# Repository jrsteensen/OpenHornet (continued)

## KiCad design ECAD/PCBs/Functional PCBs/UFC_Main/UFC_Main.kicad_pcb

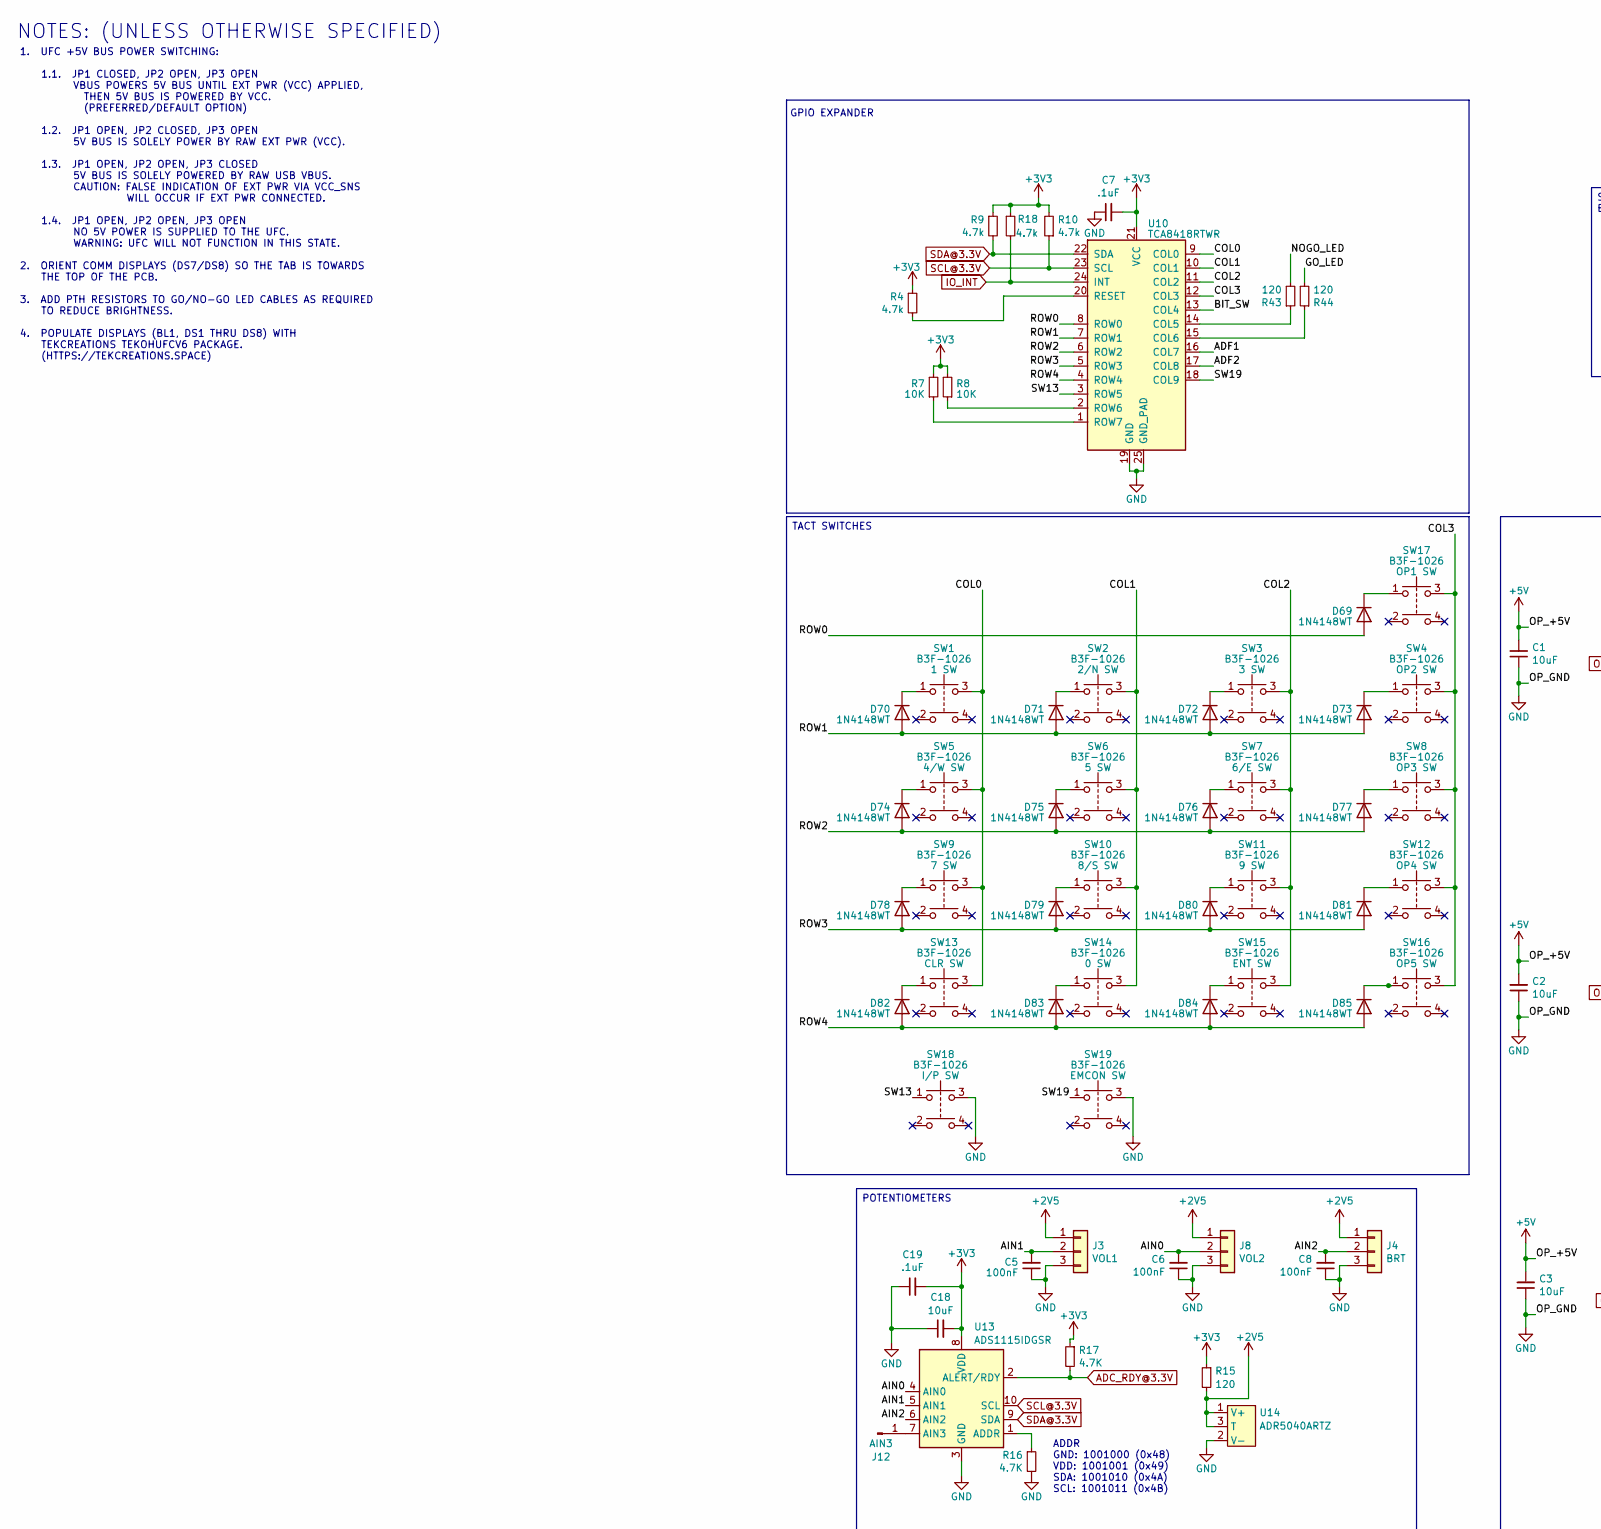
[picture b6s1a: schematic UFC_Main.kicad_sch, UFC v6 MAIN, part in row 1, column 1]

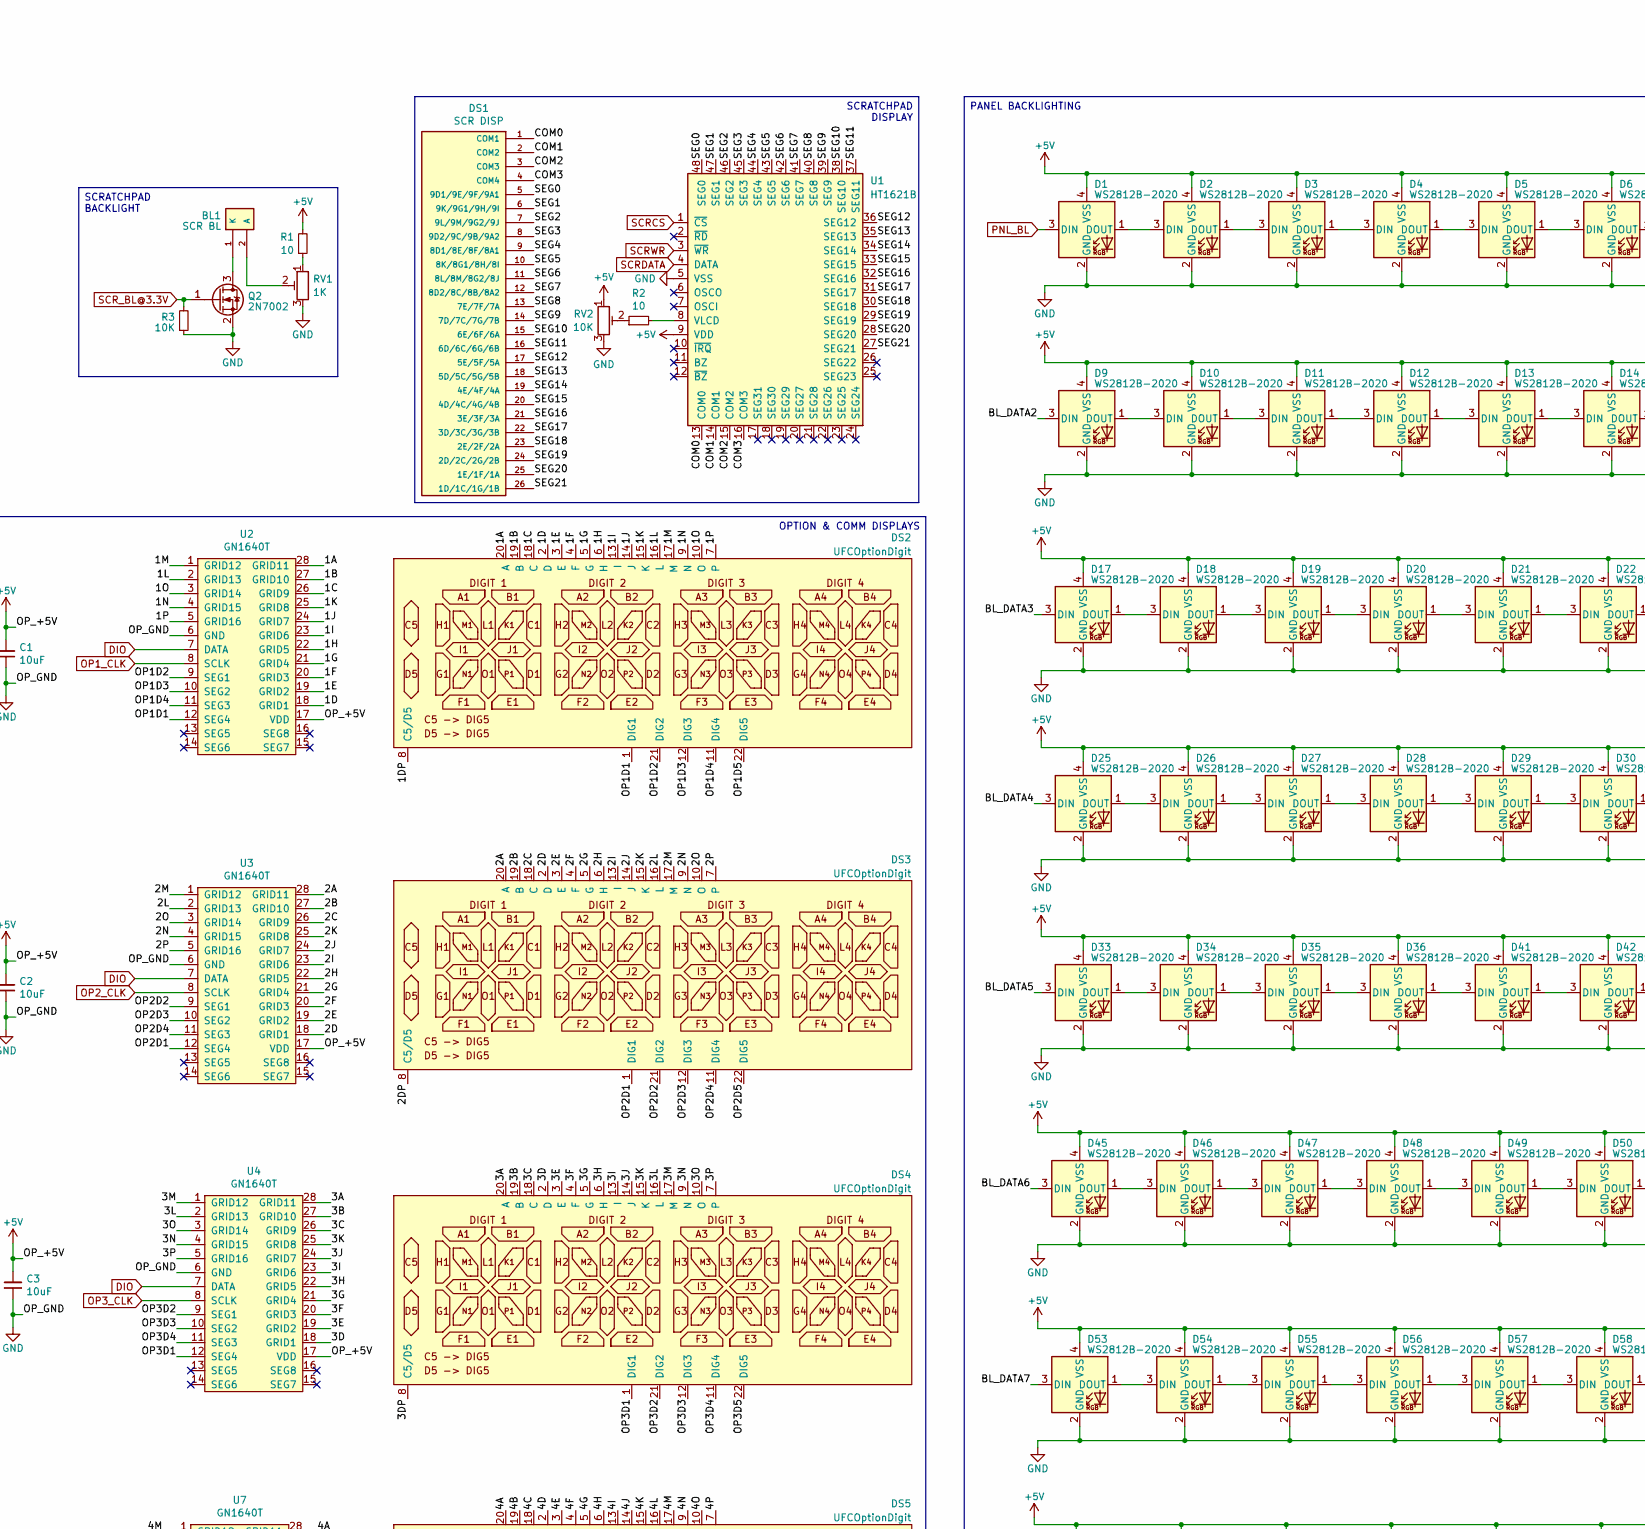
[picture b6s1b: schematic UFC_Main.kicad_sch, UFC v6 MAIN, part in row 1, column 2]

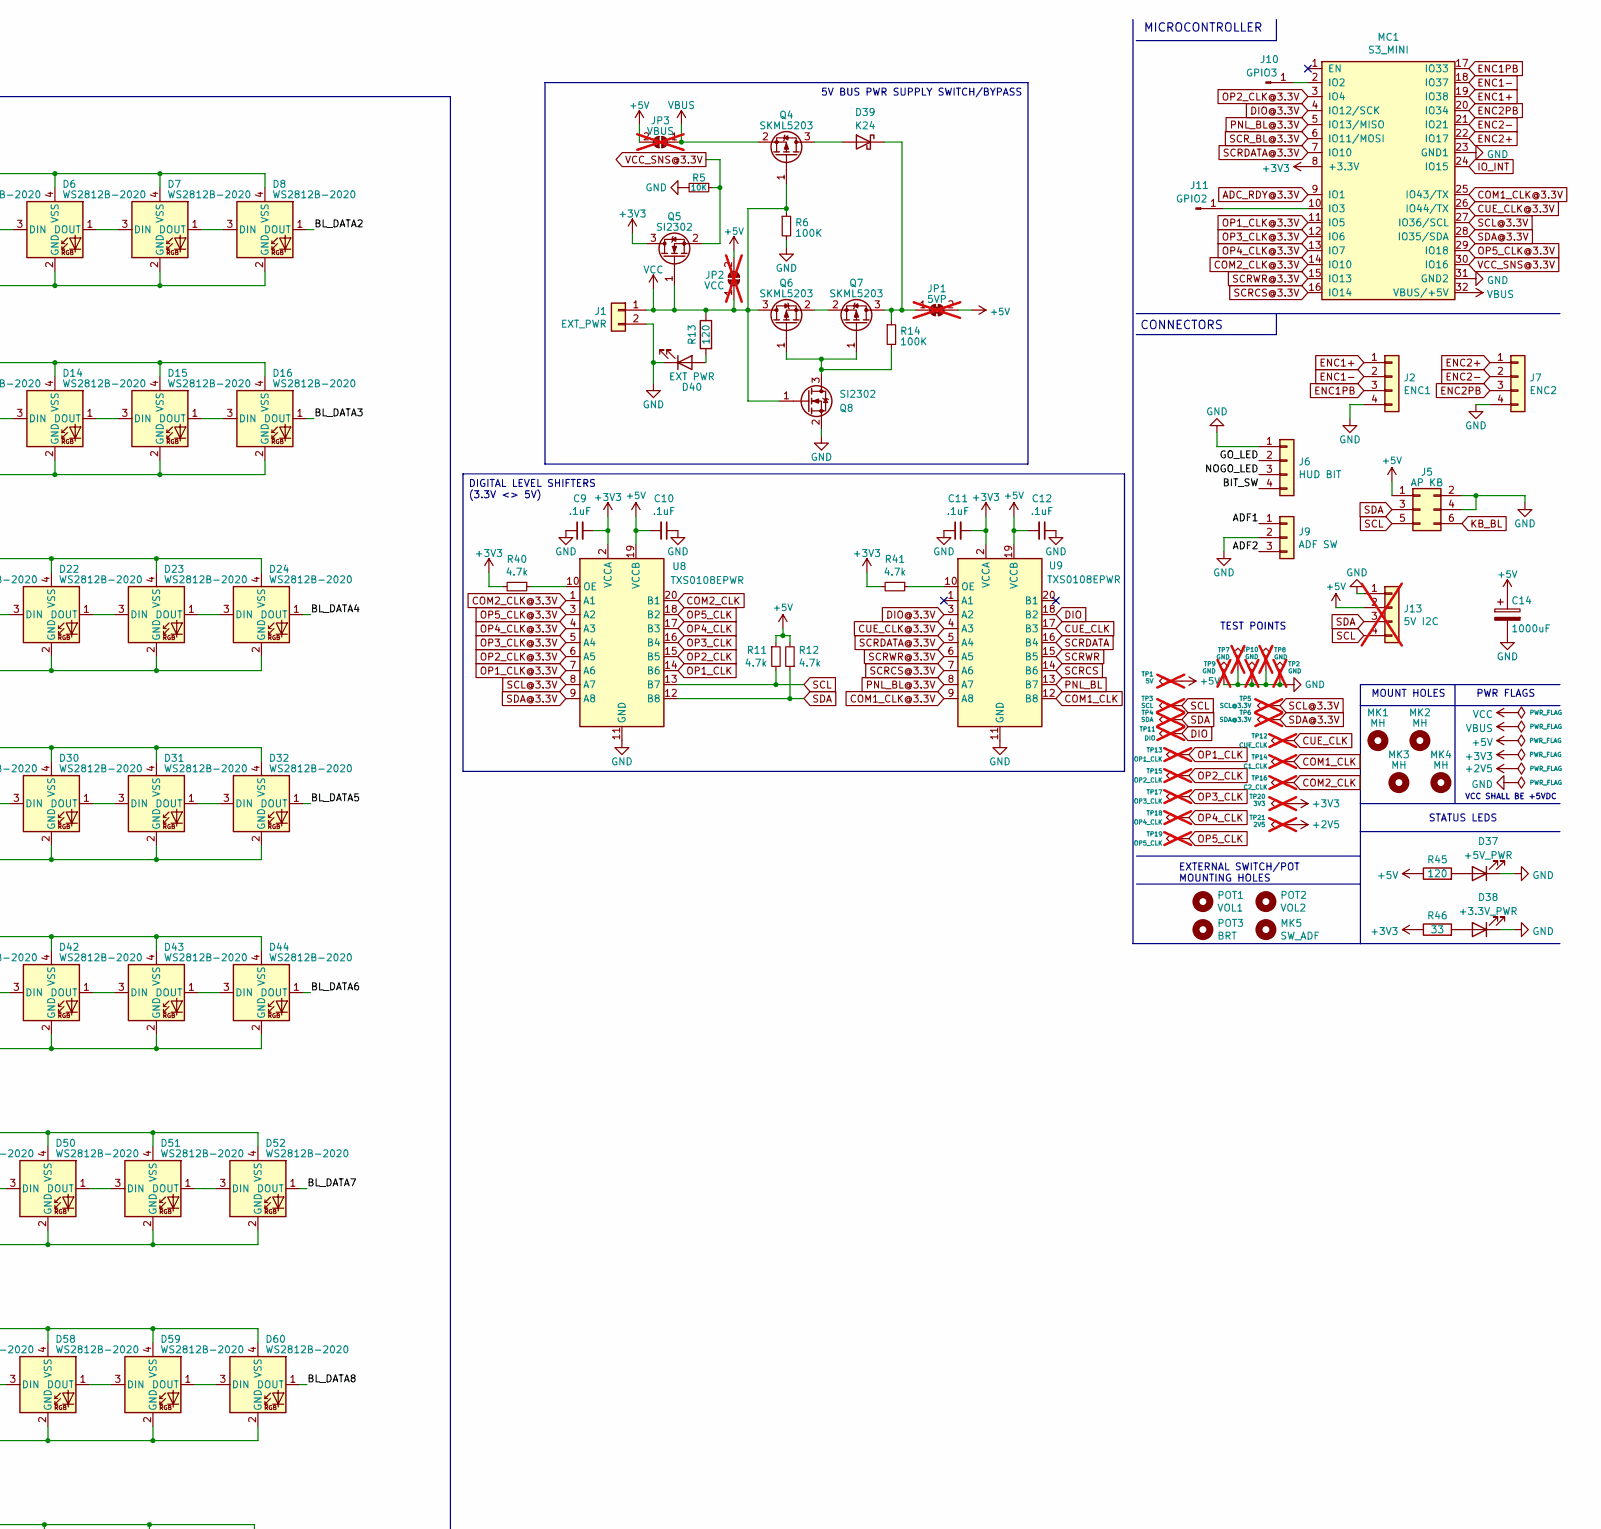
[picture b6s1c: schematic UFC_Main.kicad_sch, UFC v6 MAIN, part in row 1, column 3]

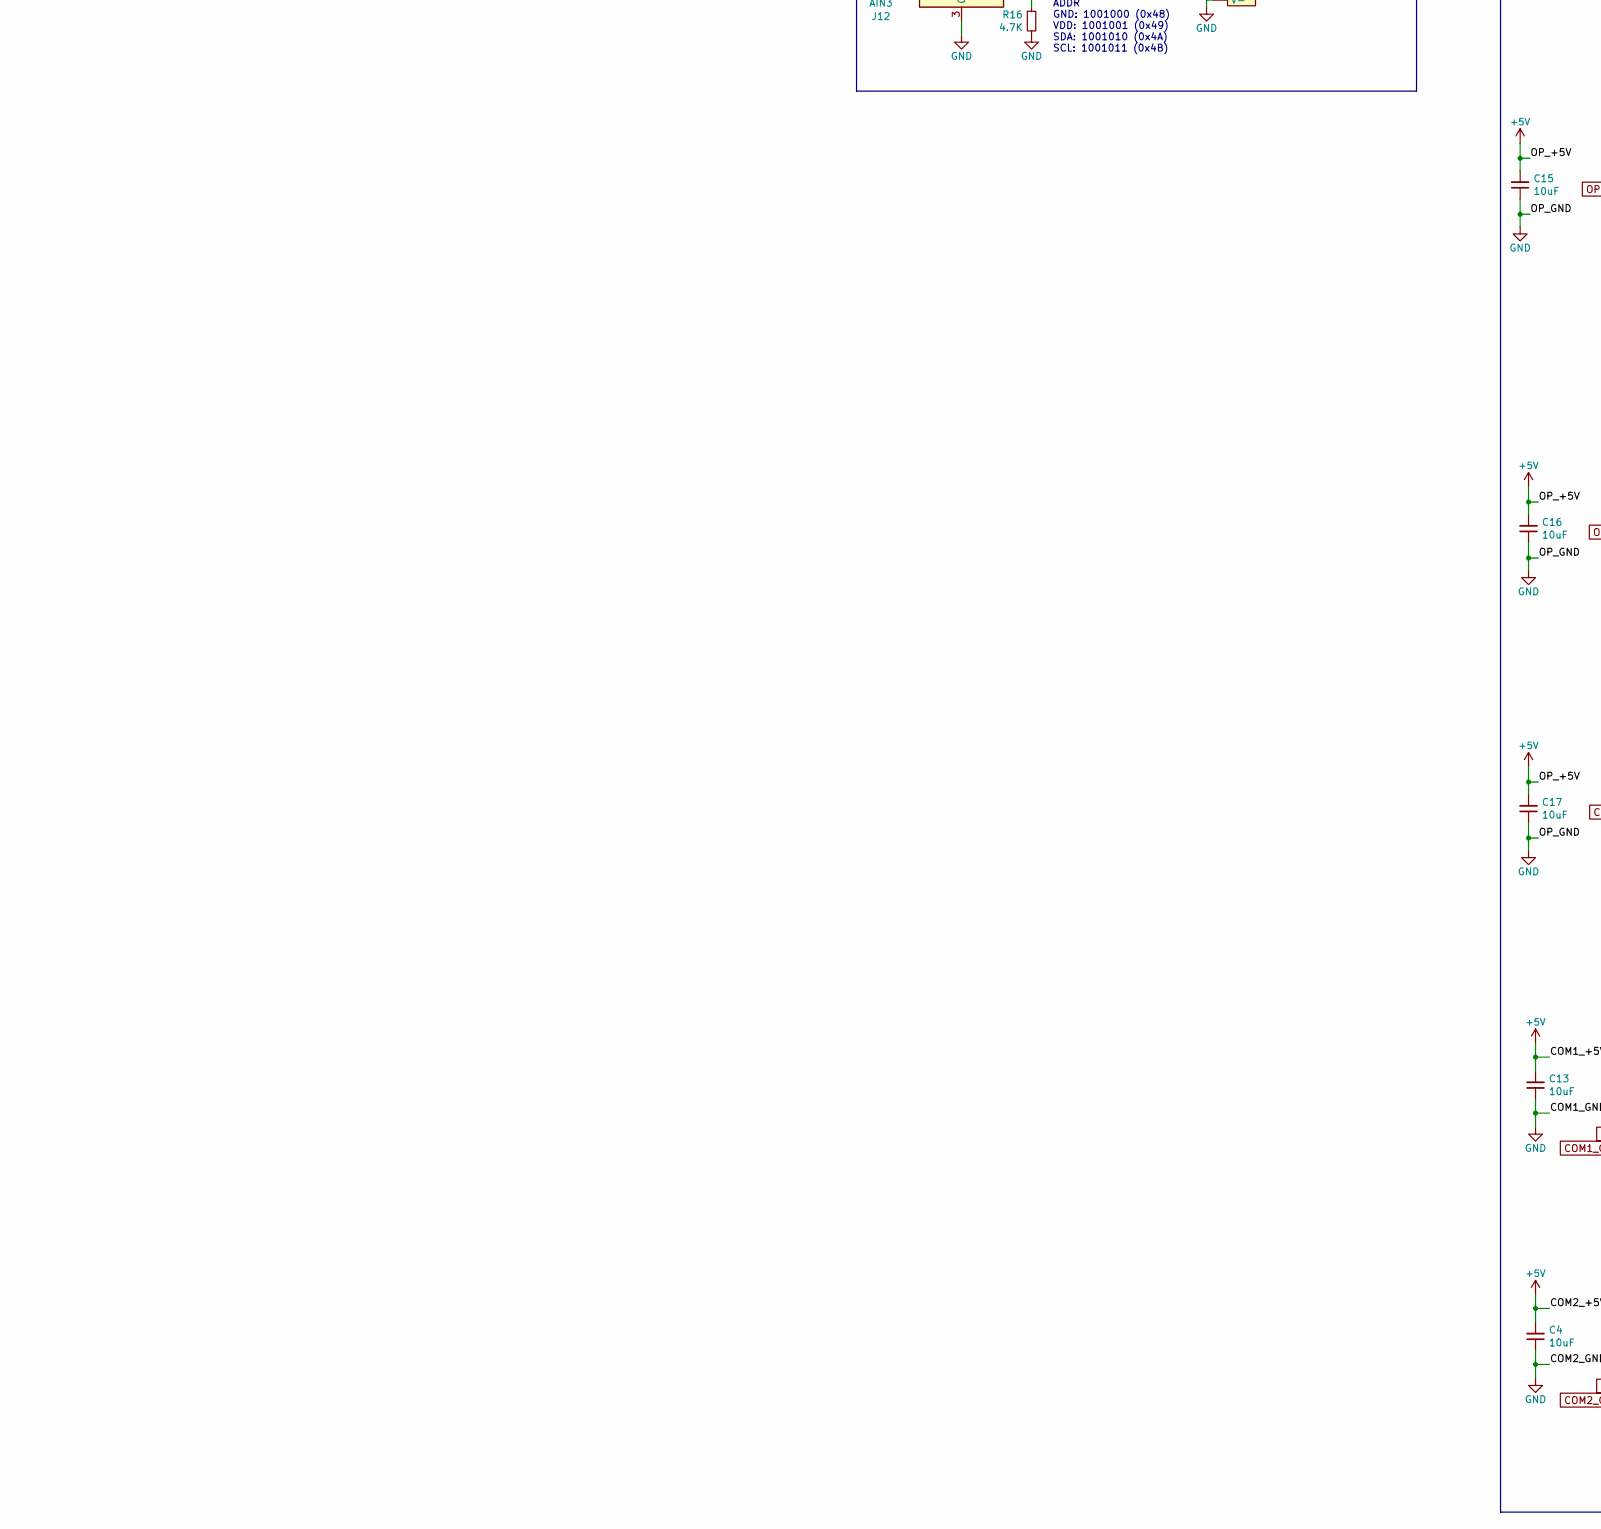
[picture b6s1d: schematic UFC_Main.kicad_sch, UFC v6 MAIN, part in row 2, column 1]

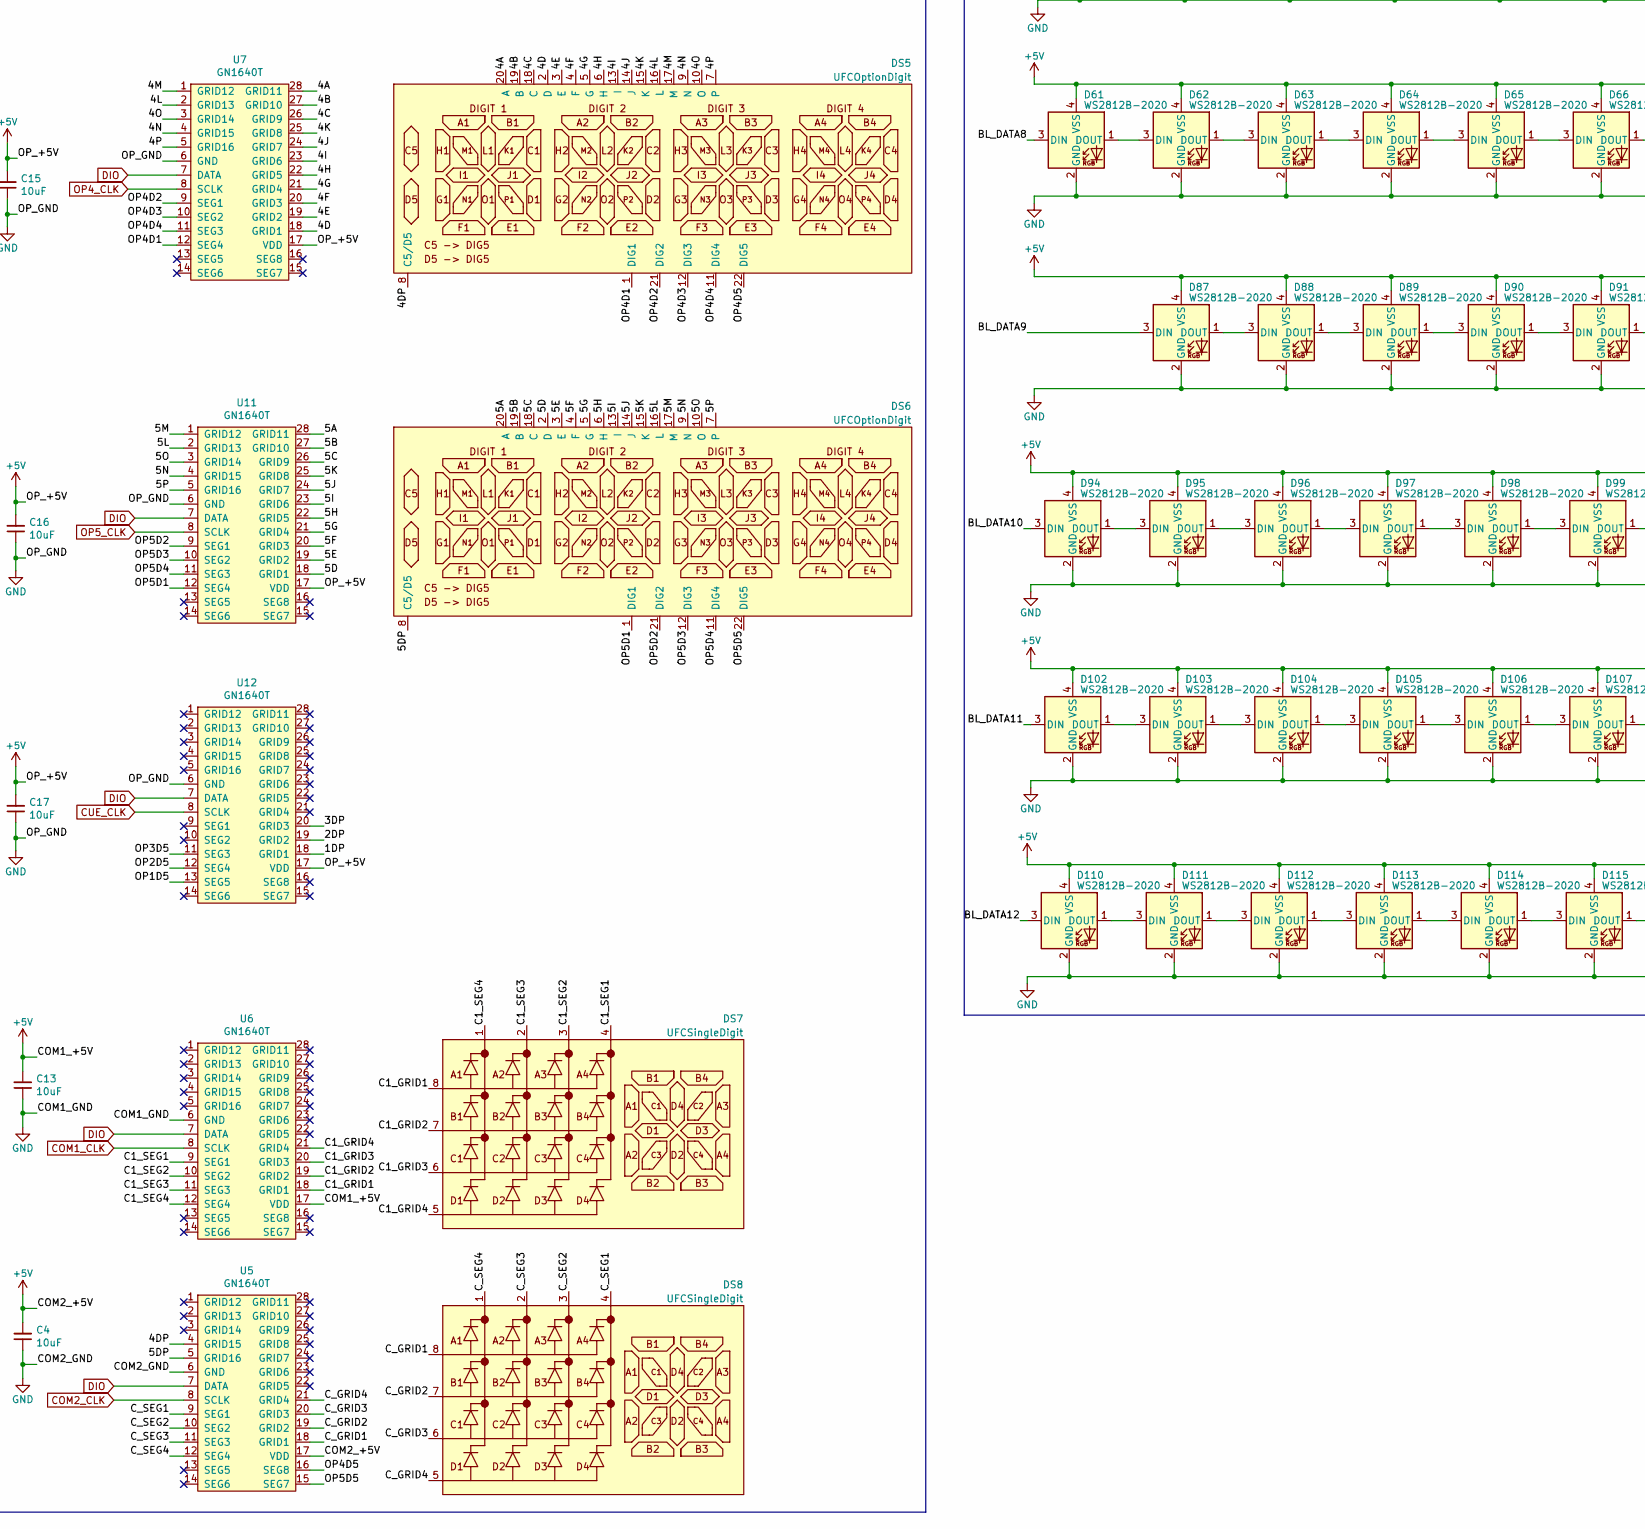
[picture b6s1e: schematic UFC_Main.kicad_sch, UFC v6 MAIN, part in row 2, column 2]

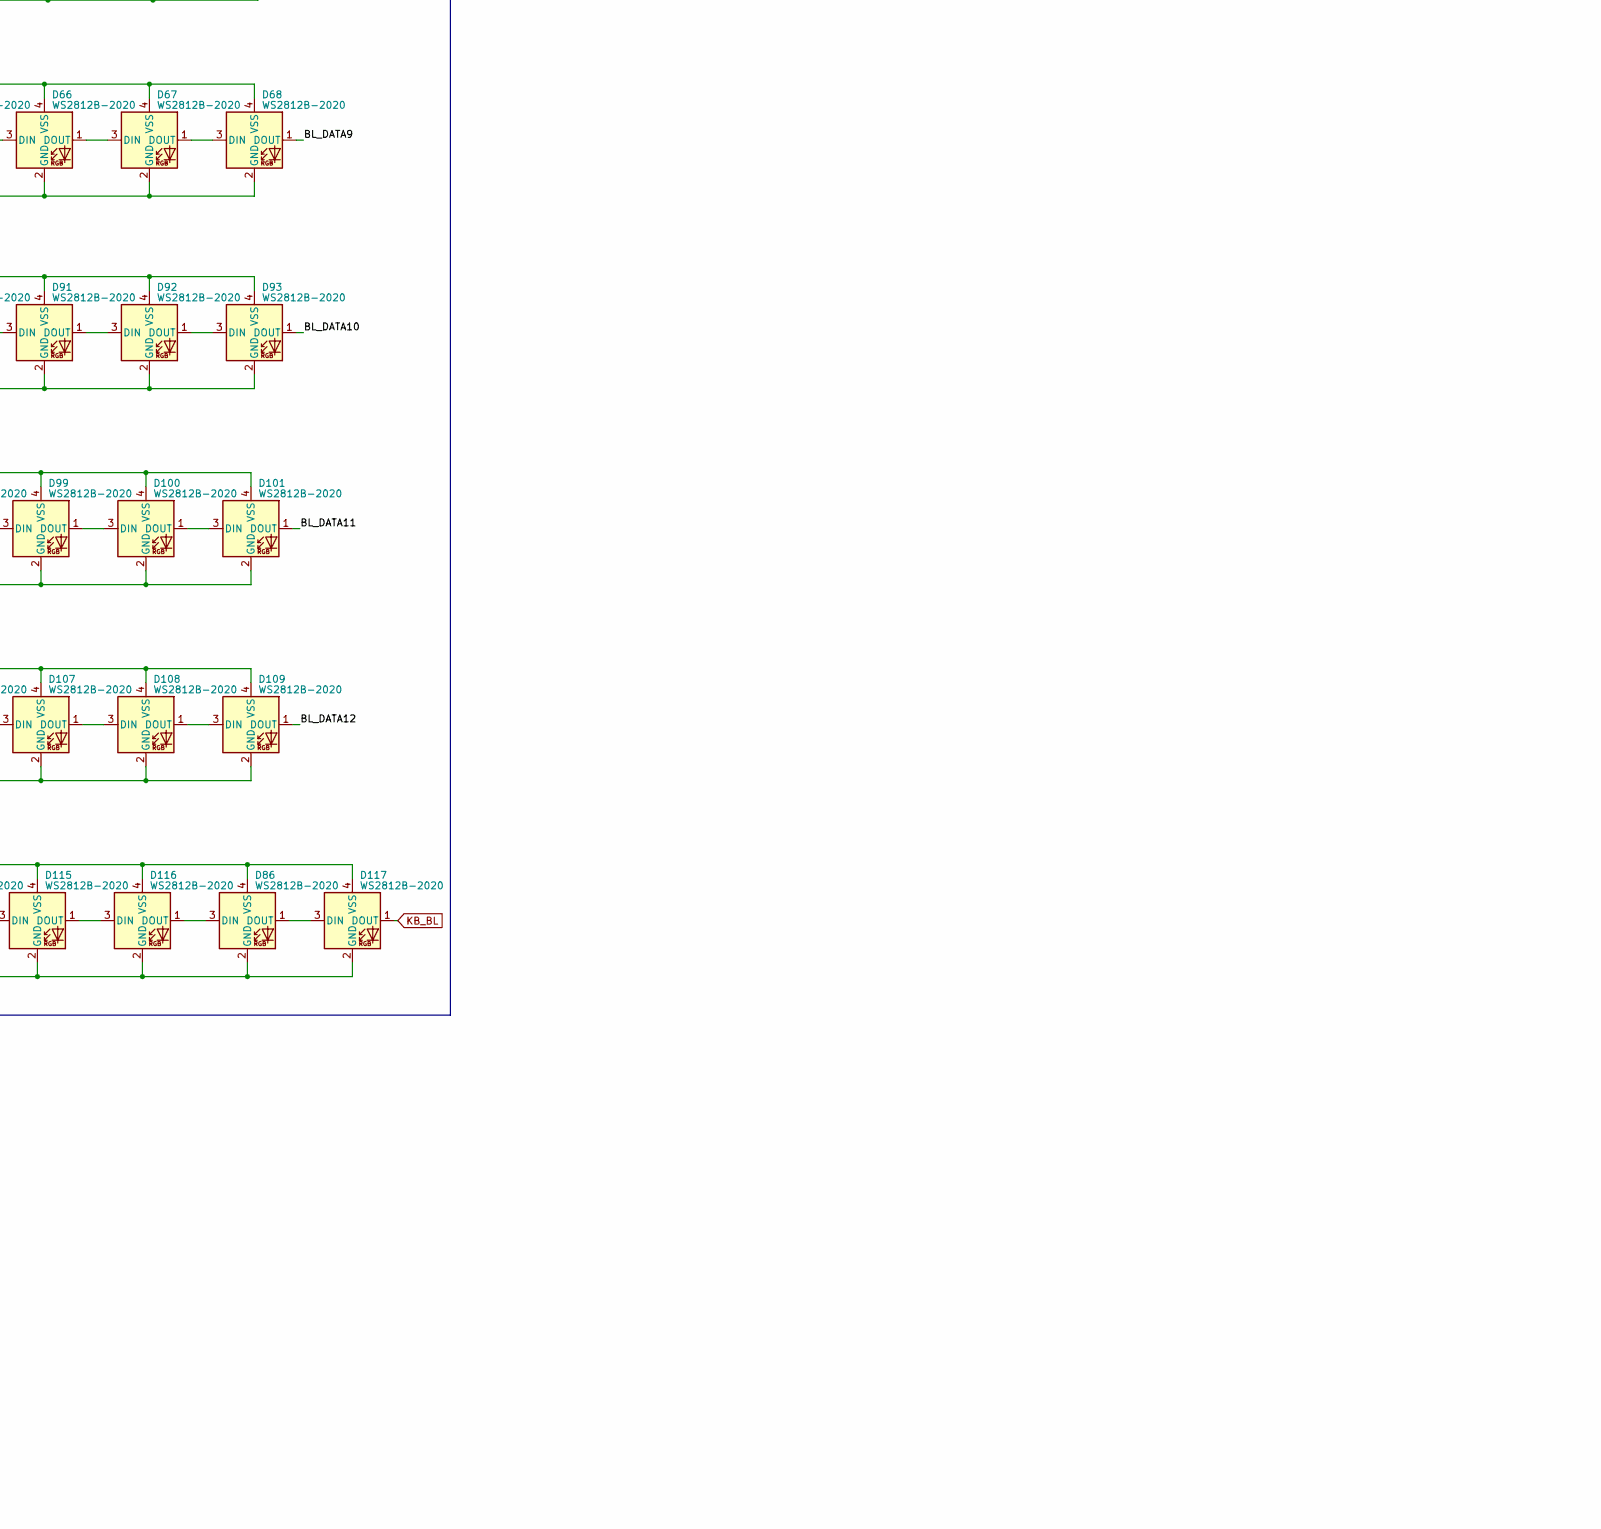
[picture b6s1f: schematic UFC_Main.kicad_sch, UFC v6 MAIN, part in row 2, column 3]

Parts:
BL1: SCR BL; SCRATCHPADBACKLIGHT
C1, C2, C3, C4, C13, C15, C16, C17: 10uF; C_0805_2012Metric; Manufacturer PN CL21A106KAYNNNE; LCSC C15850
C5, C6, C8: 100nF; C_0402_1005Metric; Manufacturer PN CL05B104KO5NNNC; LCSC C1525
C7, C9, C10, C11, C12, C19: .1uF; C_0603_1608Metric; Manufacturer PN CC0603KRX7R9BB104; LCSC C14663
C14: 1000uF; CP_Elec_8x10; Manufacturer PN UWT0J102MNL1GS; LCSC C445083
C18: 10uF; C_0402_1005Metric; Manufacturer PN CL21A106KAYNNNE; LCSC C15525
D1, D2, D3, D4, D5, D6, D7, D8, D9, D10, D11, D12, D13, D14, D15, D16, D17, D18, D19, D20, D21, D22, D23, D24, D25, D26, D27, D28, D29, D30, D31, D32, D33, D34, D35, D36, D41, D42, D43, D44, D45, D46, D47, D48, D49, D50, D51, D52, D53, D54, D55, D56, D57, D58, D59, D60, D61, D62, D63, D64, D65, D66, D67, D68, D86, D87, D88, D89, D90, D91, D92, D93, D94, D95, D96, D97, D98, D99, D100, D101, D102, D103, D104, D105, D106, D107, D108, D109, D110, D111, D112, D113, D114, D115, D116, D117: WS2812B-2020; LED_WS2812B-2020_PLCC4_2.0x2.0mm; Manufacturer PN WS2812B-2020-V6; LCSC C52917434
D37: +5V_PWR; LED_0603_1608Metric_Pad1.05x0.95mm_HandSolder; Manufacturer PN 19-217/GHC-YR1S2/3T; LCSC C72043
D38: +3.3V_PWR; LED_0603_1608Metric_Pad1.05x0.95mm_HandSolder; Manufacturer PN 19-217/GHC-YR1S2/3T; LCSC C72043
D39: K24; D_SOD-123F; Manufacturer PN K24; LCSC C908664
D40: EXT PWR; LED_0603_1608Metric_Pad1.05x0.95mm_HandSolder; Manufacturer PN 19-217/GHC-YR1S2/3T; LCSC C72043
D69, D70, D71, D72, D73, D74, D75, D76, D77, D78, D79, D80, D81, D82, D83, D84, D85: 1N4148WT; D_SOD-523; Manufacturer PN 1N4148WT; LCSC C727112
DS1: SCR DISP; SCRATCHPADLCD
DS2, DS3, DS4, DS5, DS6: UFCOptionDigit; UFCOptionDigitV3
DS7, DS8: UFCSingleDigit
J1: EXT_PWR; PinHeader_1x02_P2.54mm_Vertical
J2: ENC1; PinHeader_1x04_P2.54mm_Vertical
J3: VOL1; PinHeader_1x03_P2.54mm_Vertical
J4: BRT; PinHeader_1x03_P2.54mm_Vertical
J5: AP KB; PinHeader_2x03_P2.54mm_Vertical
J6: HUD BIT; PinHeader_1x04_P2.54mm_Vertical
J7: ENC2; PinHeader_1x04_P2.54mm_Vertical
J8: VOL2; PinHeader_1x03_P2.54mm_Vertical
J9: ADF SW; PinHeader_1x03_P2.54mm_Vertical
J10: GPIO3; SolderWirePad_1x01_SMD_1x2mm
J11: GPIO2; SolderWirePad_1x01_SMD_1x2mm
J12: AIN3; SolderWirePad_1x01_SMD_1x2mm
J13: 5V I2C; PinHeader_1x04_P2.54mm_Vertical; not fitted
JP1: 5VP; SolderJumper-2_P1.3mm_Bridged2Bar_Pad1.0x1.5mm; not fitted
JP2: VCC; SolderJumper-2_P1.3mm_Open_Pad1.0x1.5mm; not fitted
JP3: VBUS; SolderJumper-2_P1.3mm_Open_Pad1.0x1.5mm; not fitted
MC1: S3_MINI; S2_MINI
MK1, MK2, MK3, MK4: MH; MountingHole_4.5mm
MK5: SW_ADF; MountingHole_6.4mm_M6
POT1: VOL1; BR10K_Pot_11mm_x_11mm
POT2: VOL2; BR10K_Pot_11mm_x_11mm
POT3: BRT; BR10K_Pot_11mm_x_11mm
Q2: 2N7002; SOT-23; Manufacturer PN 2N7002; LCSC C8545
Q4, Q6, Q7: SKML5203; SOT-23; Manufacturer PN ME2328-G; LCSC C475707
Q5, Q8: SI2302; SOT-23; Manufacturer PN SI2302; LCSC C2891732
R1: 10; R_2512_6332Metric_Pad1.40x3.35mm_HandSolder; Manufacturer PN 352210RJT
R2: 10; C_0402_1005Metric_Pad0.74x0.62mm_HandSolder; Manufacturer PN 0402WGF100JTCE; LCSC C25077
R3, R5, R7, R8: 10K; R_0603_1608Metric; Manufacturer PN 0603WAF1002T5E; LCSC C25804
R4, R9, R10, R11, R12, R18, R40, R41: 4.7k; R_0603_1608Metric; Manufacturer PN 0603WAF4701T5E; LCSC C23162
R6, R14: 100K; R_0402_1005Metric; Manufacturer PN 0402WGF1003TCE; LCSC C25741
R13, R15, R43, R44, R45: 120; R_0603_1608Metric; Manufacturer PN 0603WAF1200T5E; LCSC C22787
R16, R17: 4.7K; R_0603_1608Metric; Manufacturer PN 0603WAF4701T5E; LCSC C23162
R46: 33; R_0402_1005Metric; Manufacturer PN 0402WGF330JTCE; LCSC C25105
RV1: 1K; Potentiometer_Bourns_3386P_Vertical; Manufacturer PN 3386P-1-102LF
RV2: 10K; Potentiometer_Bourns_3386P_Vertical; Manufacturer PN 3386P-1-103LF
SW1, SW2, SW3, SW4, SW5, SW6, SW7, SW8, SW9, SW10, SW11, SW12, SW13, SW14, SW15, SW16, SW17, SW18, SW19: B3F-1026; Omron_B3F-1026; Manufacturer PN B3F-1026
TP1: 5V; TestPoint_THTPad_D1.5mm_Drill0.7mm; not fitted
TP2, TP7, TP8, TP9, TP10: GND; TestPoint_THTPad_D1.5mm_Drill0.7mm; not fitted
TP3: SCL; TestPoint_THTPad_D1.5mm_Drill0.7mm; not fitted
TP4: SDA; TestPoint_THTPad_D1.5mm_Drill0.7mm; not fitted
TP5: SCL@3.3V; TestPoint_THTPad_D1.5mm_Drill0.7mm; not fitted
TP6: SDA@3.3V; TestPoint_THTPad_D1.5mm_Drill0.7mm; not fitted
TP11: DIO; TestPoint_THTPad_D1.5mm_Drill0.7mm; not fitted
TP12: CUE_CLK; TestPoint_THTPad_D1.5mm_Drill0.7mm; not fitted
TP13: OP1_CLK; TestPoint_THTPad_D1.5mm_Drill0.7mm; not fitted
TP14: C1_CLK; TestPoint_THTPad_D1.5mm_Drill0.7mm; not fitted
TP15: OP2_CLK; TestPoint_THTPad_D1.5mm_Drill0.7mm; not fitted
TP16: C2_CLK; TestPoint_THTPad_D1.5mm_Drill0.7mm; not fitted
TP17: OP3_CLK; TestPoint_THTPad_D1.5mm_Drill0.7mm; not fitted
TP18: OP4_CLK; TestPoint_THTPad_D1.5mm_Drill0.7mm; not fitted
TP19: OP5_CLK; TestPoint_THTPad_D1.5mm_Drill0.7mm; not fitted
TP20: 3V3; TestPoint_THTPad_D1.5mm_Drill0.7mm; not fitted
TP21: 2V5; TestPoint_THTPad_D1.5mm_Drill0.7mm; not fitted
U1: HT1621B; LQFP-48_7x7mm_P0.5mm; LCSC C7532
U2, U3, U4, U5, U6, U7, U11, U12: GN1640T; SSOP-28_3.9x9.9mm_P0.635mm; LCSC C2758330
U8, U9: TXS0108EPWR; TSSOP-20_4.4x6.5mm_P0.65mm; Manufacturer PN TXS0108EPWR; LCSC C17206
U10: TCA8418RTWR; WQFN-24-1EP_4x4mm_P0.5mm_EP2.45x2.45mm; Manufacturer PN TCA8418RTWR; LCSC C138713
U13: ADS1115IDGSR; VSSOP-10_3x3mm_P0.5mm; LCSC C37593
U14: ADR5040ARTZ; SOT-23-3; LCSC C144273

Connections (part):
+2V5: J3.1, J4.1, J8.1, R15.2, TP21.1 (1_1), U14.1 (V+), U14.3 (T)
+3V3: C7.2, C9.2, C11.2, C18.2, C19.2, MC1.8 (+3.3V), Q5.3 (D), R4.1, R7.2, R8.2, R9.1, R10.2, R15.1, R17.1, R18.1, R40.2, R41.2, R46.1, TP20.1 (1_1), U8.2 (VCCA), U9.2 (VCCA), U10.21 (VCC), U13.8 (VDD)
+5V: C1.2, C2.2, C3.2, C4.2, C10.2, C12.2, C13.2, C14.1, C15.2, C16.2, C17.2, D1.4 (VSS), D2.4 (VSS), D3.4 (VSS), D4.4 (VSS), D5.4 (VSS), D6.4 (VSS), D7.4 (VSS), D8.4 (VSS), D9.4 (VSS), D10.4 (VSS), D11.4 (VSS), D12.4 (VSS), D13.4 (VSS), D14.4 (VSS), D15.4 (VSS), D16.4 (VSS), D17.4 (VSS), D18.4 (VSS), D19.4 (VSS), D20.4 (VSS), D21.4 (VSS), D22.4 (VSS), D23.4 (VSS), D24.4 (VSS), D25.4 (VSS), D26.4 (VSS), D27.4 (VSS), D28.4 (VSS), D29.4 (VSS), D30.4 (VSS), D31.4 (VSS), D32.4 (VSS), D33.4 (VSS), D34.4 (VSS), D35.4 (VSS), D36.4 (VSS), D41.4 (VSS), D42.4 (VSS), D43.4 (VSS), D44.4 (VSS), D45.4 (VSS), D46.4 (VSS), D47.4 (VSS), D48.4 (VSS), D49.4 (VSS), D50.4 (VSS), D51.4 (VSS), D52.4 (VSS), D53.4 (VSS), D54.4 (VSS), D55.4 (VSS), D56.4 (VSS), D57.4 (VSS), D58.4 (VSS), D59.4 (VSS), D60.4 (VSS), D61.4 (VSS), D62.4 (VSS), D63.4 (VSS), D64.4 (VSS), D65.4 (VSS), D66.4 (VSS), D67.4 (VSS), D68.4 (VSS), D86.4 (VSS), D87.4 (VSS), D88.4 (VSS), D89.4 (VSS), D90.4 (VSS), D91.4 (VSS), D92.4 (VSS), D93.4 (VSS), D94.4 (VSS)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
/1A: DS2.20 (A), U2.28 (GRID11)
/1B: DS2.19 (B), U2.27 (GRID10)
/1C: DS2.18 (C), U2.26 (GRID9)
/1D: DS2.2 (D), U2.18 (GRID1)
/1DP: DS2.8 (C5/D5), U12.18 (GRID1)
/1E: DS2.3 (E), U2.19 (GRID2)
/1F: DS2.4 (F), U2.20 (GRID3)
/1G: DS2.5 (G), U2.21 (GRID4)
/1H: DS2.6 (H), U2.22 (GRID5)
/1I: DS2.13 (I), U2.23 (GRID6)
/1J: DS2.14 (J), U2.24 (GRID7)
/1K: DS2.15 (K), U2.25 (GRID8)
/1L: DS2.16 (L), U2.2 (GRID13)
/1M: DS2.17 (M), U2.1 (GRID12)
/1N: DS2.9 (N), U2.4 (GRID15)
/1O: DS2.10 (O), U2.3 (GRID14)
/1P: DS2.7, U2.5 (GRID16)
/2A: DS3.20 (A), U3.28 (GRID11)
/2B: DS3.19 (B), U3.27 (GRID10)
/2C: DS3.18 (C), U3.26 (GRID9)
/2D: DS3.2 (D), U3.18 (GRID1)
/2DP: DS3.8 (C5/D5), U12.19 (GRID2)
/2E: DS3.3 (E), U3.19 (GRID2)
/2F: DS3.4 (F), U3.20 (GRID3)
/2G: DS3.5 (G), U3.21 (GRID4)
/2H: DS3.6 (H), U3.22 (GRID5)
/2I: DS3.13 (I), U3.23 (GRID6)
/2J: DS3.14 (J), U3.24 (GRID7)
/2K: DS3.15 (K), U3.25 (GRID8)
/2L: DS3.16 (L), U3.2 (GRID13)
/2M: DS3.17 (M), U3.1 (GRID12)
/2N: DS3.9 (N), U3.4 (GRID15)
/2O: DS3.10 (O), U3.3 (GRID14)
/2P: DS3.7, U3.5 (GRID16)
/3A: DS4.20 (A), U4.28 (GRID11)
/3B: DS4.19 (B), U4.27 (GRID10)
/3C: DS4.18 (C), U4.26 (GRID9)
/3D: DS4.2 (D), U4.18 (GRID1)
/3DP: DS4.8 (C5/D5), U12.20 (GRID3)
/3E: DS4.3 (E), U4.19 (GRID2)
/3F: DS4.4 (F), U4.20 (GRID3)
/3G: DS4.5 (G), U4.21 (GRID4)
/3H: DS4.6 (H), U4.22 (GRID5)
/3I: DS4.13 (I), U4.23 (GRID6)
/3J: DS4.14 (J), U4.24 (GRID7)
/3K: DS4.15 (K), U4.25 (GRID8)
/3L: DS4.16 (L), U4.2 (GRID13)
/3M: DS4.17 (M), U4.1 (GRID12)
/3N: DS4.9 (N), U4.4 (GRID15)
/3O: DS4.10 (O), U4.3 (GRID14)
/3P: DS4.7, U4.5 (GRID16)
/4A: DS5.20 (A), U7.28 (GRID11)
/4B: DS5.19 (B), U7.27 (GRID10)
/4C: DS5.18 (C), U7.26 (GRID9)
/4D: DS5.2 (D), U7.18 (GRID1)
/4DP: DS5.8 (C5/D5), U5.4 (GRID15)
/4E: DS5.3 (E), U7.19 (GRID2)
/4F: DS5.4 (F), U7.20 (GRID3)
/4G: DS5.5 (G), U7.21 (GRID4)
/4H: DS5.6 (H), U7.22 (GRID5)
/4I: DS5.13 (I), U7.23 (GRID6)
/4J: DS5.14 (J), U7.24 (GRID7)
/4K: DS5.15 (K), U7.25 (GRID8)
/4L: DS5.16 (L), U7.2 (GRID13)
/4M: DS5.17 (M), U7.1 (GRID12)
/4N: DS5.9 (N), U7.4 (GRID15)
/4O: DS5.10 (O), U7.3 (GRID14)
/4P: DS5.7, U7.5 (GRID16)
/5A: DS6.20 (A), U11.28 (GRID11)
/5B: DS6.19 (B), U11.27 (GRID10)
/5C: DS6.18 (C), U11.26 (GRID9)
/5D: DS6.2 (D), U11.18 (GRID1)
/5DP: DS6.8 (C5/D5), U5.5 (GRID16)
/5E: DS6.3 (E), U11.19 (GRID2)
/5F: DS6.4 (F), U11.20 (GRID3)
/5G: DS6.5 (G), U11.21 (GRID4)
/5H: DS6.6 (H), U11.22 (GRID5)
/5I: DS6.13 (I), U11.23 (GRID6)
/5J: DS6.14 (J), U11.24 (GRID7)
/5K: DS6.15 (K), U11.25 (GRID8)
/5L: DS6.16 (L), U11.2 (GRID13)
/5M: DS6.17 (M), U11.1 (GRID12)
/5N: DS6.9 (N), U11.4 (GRID15)
/5O: DS6.10 (O), U11.3 (GRID14)
/5P: DS6.7, U11.5 (GRID16)
/ADF1: J9.1, U10.16 (COL7)
/ADF2: J9.3, U10.17 (COL8)
/AIN0: C6.2, J8.2, U13.4 (AIN0)
/AIN1: C5.2, J3.2, U13.5 (AIN1)
/AIN2: C8.2, J4.2, U13.6 (AIN2)
/BIT_SW: J6.4, U10.13 (COL4)
/BL_DATA2: D8.1 (DOUT), D9.3 (DIN)
/BL_DATA3: D16.1 (DOUT), D17.3 (DIN)
/BL_DATA4: D24.1 (DOUT), D25.3 (DIN)
/BL_DATA5: D32.1 (DOUT), D33.3 (DIN)
/BL_DATA6: D44.1 (DOUT), D45.3 (DIN)
/BL_DATA7: D52.1 (DOUT), D53.3 (DIN)
/BL_DATA8: D60.1 (DOUT), D61.3 (DIN)
/BL_DATA9: D68.1 (DOUT), D87.3 (DIN)
/BL_DATA10: D93.1 (DOUT), D94.3 (DIN)
/BL_DATA11: D101.1 (DOUT), D102.3 (DIN)
/BL_DATA12: D109.1 (DOUT), D110.3 (DIN)
/C1_GRID1: DS7.8, U6.18 (GRID1)
/C1_GRID2: DS7.7, U6.19 (GRID2)
/C1_GRID3: DS7.6, U6.20 (GRID3)
/C1_GRID4: DS7.5, U6.21 (GRID4)
/C1_SEG1: DS7.4, U6.9 (SEG1)
/C1_SEG2: DS7.3, U6.10 (SEG2)
/C1_SEG3: DS7.2, U6.11 (SEG3)
/C1_SEG4: DS7.1, U6.12 (SEG4)
/COL0: SW1.3, SW5.3, SW9.3, SW13.3, U10.9 (COL0)
/COL1: SW2.3, SW6.3, SW10.3, SW14.3, U10.10 (COL1)
/COL2: SW3.3, SW7.3, SW11.3, SW15.3, U10.11 (COL2)
/COL3: SW4.3, SW8.3, SW12.3, SW16.3, SW17.3, U10.12 (COL3)
/COM0: DS1.1 (COM1), U1.13 (COM0)
/COM1: DS1.2 (COM2), U1.14 (COM1)
/COM2: DS1.3 (COM3), U1.15 (COM2)
/COM3: DS1.4 (COM4), U1.16 (COM3)
/C_GRID1: DS8.8, U5.18 (GRID1)
/C_GRID2: DS8.7, U5.19 (GRID2)
/C_GRID3: DS8.6, U5.20 (GRID3)
/C_GRID4: DS8.5, U5.21 (GRID4)
/C_SEG1: DS8.4, U5.9 (SEG1)
/C_SEG2: DS8.3, U5.10 (SEG2)
/C_SEG3: DS8.2, U5.11 (SEG3)
/C_SEG4: DS8.1, U5.12 (SEG4)
/GO_LED: J6.2, R44.2
/NOGO_LED: J6.3, R43.2
/OP1D1: DS2.1 (DIG1), U2.12 (SEG4)
/OP1D2: DS2.21 (DIG2), U2.9 (SEG1)
/OP1D3: DS2.12 (DIG3), U2.10 (SEG2)
/OP1D4: DS2.11 (DIG4), U2.11 (SEG3)
/OP1D5: DS2.22 (DIG5), U12.13 (SEG5)
/OP2D1: DS3.1 (DIG1), U3.12 (SEG4)
/OP2D2: DS3.21 (DIG2), U3.9 (SEG1)
/OP2D3: DS3.12 (DIG3), U3.10 (SEG2)
/OP2D4: DS3.11 (DIG4), U3.11 (SEG3)
/OP2D5: DS3.22 (DIG5), U12.12 (SEG4)
/OP3D1: DS4.1 (DIG1), U4.12 (SEG4)
/OP3D2: DS4.21 (DIG2), U4.9 (SEG1)
/OP3D3: DS4.12 (DIG3), U4.10 (SEG2)
/OP3D4: DS4.11 (DIG4), U4.11 (SEG3)
/OP3D5: DS4.22 (DIG5), U12.11 (SEG3)
/OP4D1: DS5.1 (DIG1), U7.12 (SEG4)
/OP4D2: DS5.21 (DIG2), U7.9 (SEG1)
/OP4D3: DS5.12 (DIG3), U7.10 (SEG2)
/OP4D4: DS5.11 (DIG4), U7.11 (SEG3)
/OP4D5: DS5.22 (DIG5), U5.16 (SEG8)
/OP5D1: DS6.1 (DIG1), U11.12 (SEG4)
/OP5D2: DS6.21 (DIG2), U11.9 (SEG1)
/OP5D3: DS6.12 (DIG3), U11.10 (SEG2)
/OP5D4: DS6.11 (DIG4), U11.11 (SEG3)
/OP5D5: DS6.22 (DIG5), U5.15 (SEG7)
/ROW0: D69.2 (A), U10.8 (ROW0)
/ROW1: D70.2 (A), D71.2 (A), D72.2 (A), D73.2 (A), U10.7 (ROW1)
/ROW2: D74.2 (A), D75.2 (A), D76.2 (A), D77.2 (A), U10.6 (ROW2)
/ROW3: D78.2 (A), D79.2 (A), D80.2 (A), D81.2 (A), U10.5 (ROW3)
/ROW4: D82.2 (A), D83.2 (A), D84.2 (A), D85.2 (A), U10.4 (ROW4)
/SEG0: DS1.5 (9D1/9E/9F/9A1), U1.48 (SEG0)
/SEG1: DS1.6 (9K/9G1/9H/9I), U1.47 (SEG1)
/SEG2: DS1.7 (9L/9M/9G2/9J), U1.46 (SEG2)
/SEG3: DS1.8 (9D2/9C/9B/9A2), U1.45 (SEG3)
/SEG4: DS1.9 (8D1/8E/8F/8A1), U1.44 (SEG4)
/SEG5: DS1.10 (8K/8G1/8H/8I), U1.43 (SEG5)
/SEG6: DS1.11 (8L/8M/8G2/8J), U1.42 (SEG6)
/SEG7: DS1.12 (8D2/8C/8B/8A2), U1.41 (SEG7)
/SEG8: DS1.13 (7E/7F/7A), U1.40 (SEG8)
/SEG9: DS1.14 (7D/7C/7G/7B), U1.39 (SEG9)
/SEG10: DS1.15 (6E/6F/6A), U1.38 (SEG10)
/SEG11: DS1.16 (6D/6C/6G/6B), U1.37 (SEG11)
/SEG12: DS1.17 (5E/5F/5A), U1.36 (SEG12)
/SEG13: DS1.18 (5D/5C/5G/5B), U1.35 (SEG13)
/SEG14: DS1.19 (4E/4F/4A), U1.34 (SEG14)
/SEG15: DS1.20 (4D/4C/4G/4B), U1.33 (SEG15)
/SEG16: DS1.21 (3E/3F/3A), U1.32 (SEG16)
/SEG17: DS1.22 (3D/3C/3G/3B), U1.31 (SEG17)
/SEG18: DS1.23 (2E/2F/2A), U1.30 (SEG18)
/SEG19: DS1.24 (2D/2C/2G/2B), U1.29 (SEG19)
/SEG20: DS1.25 (1E/1F/1A), U1.28 (SEG20)
/SEG21: DS1.26 (1D/1C/1G/1B), U1.27 (SEG21)
/SW13: SW18.1, U10.3 (ROW5)
/SW19: SW19.1, U10.18 (COL9)
ADC_RDY@3.3V: MC1.9 (IO1), R17.2, U13.2 (ALERT/RDY)
COM1_CLK: TP14.1 (1_1), U6.8 (SCLK), U9.12 (B8)
COM1_CLK@3.3V: MC1.25 (IO43/TX), U9.9 (A8)
COM2_CLK: TP16.1 (1_1), U5.8 (SCLK), U8.20 (B1)
COM2_CLK@3.3V: MC1.14 (IO10), U8.1 (A1)
CUE_CLK: TP12.1 (1_1), U9.17 (B3), U12.8 (SCLK)
CUE_CLK@3.3V: MC1.26 (IO44/TX), U9.4 (A3)
DIO: TP11.1 (1_1), U2.7 (DATA), U3.7 (DATA), U4.7 (DATA), U5.7 (DATA), U6.7 (DATA), U7.7 (DATA), U9.18 (B2), U11.7 (DATA), U12.7 (DATA)
DIO@3.3V: MC1.4 (IO12/SCK), U9.3 (A2)
ENC1+: J2.1, MC1.19 (IO38)
ENC1-: J2.2, MC1.18 (IO37)
ENC1PB: J2.3, MC1.17 (IO33)
ENC2+: J7.1, MC1.22 (IO17)
ENC2-: J7.2, MC1.21 (IO21)
ENC2PB: J7.3, MC1.20 (IO34)
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
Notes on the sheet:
ADDR GND: 1001000 (0x48) VDD: 1001001 (0x49) SDA: 1001010 (0x4A) SCL: 1001011 (0x4B)
NOTES: (UNLESS OTHERWISE SPECIFIED)
EXTERNAL SWITCH/POT MOUNTING HOLES
MICROCONTROLLER
CONNECTORS
STATUS LEDS
TEST POINTS
MOUNT HOLES
PWR FLAGS
VCC SHALL BE +5VDC
1. UFC +5V BUS POWER SWITCHING: 1.1. JP1 CLOSED, JP2 OPEN, JP3 OPEN VBUS POWERS 5V BUS UNTIL EXT PWR (VCC) APPLIED, THEN 5V BUS IS POWERED BY VCC. (PREFERRED/DEFAULT OPTION) 1.2. JP1 OPEN, JP2 CLOSED, JP3 OPEN 5V BUS IS SOLELY POWER BY RAW EXT PWR (VCC). 1.3. JP1 OPEN, JP2 OPEN, JP3 CLOSED 5V BUS I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
GPIO EXPANDER
POTENTIOMETERS
5V BUS PWR SUPPLY SWITCH/BYPASS
SCRATCHPAD DISPLAY
SCRATCHPAD BACKLIGHT
TACT SWITCHES
PANEL BACKLIGHTING
DIGITAL LEVEL SHIFTERS (3.3V <> 5V)
OPTION & COMM DISPLAYS
